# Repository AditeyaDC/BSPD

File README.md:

# BSPD RZ-XX6-C/E — Brake System Plausibility Device
**Ashwa Racing 27**  
Designed by Aditeya Sarkar

---

## What is a BSPD?

The Brake System Plausibility Device is a mandatory safety circuit in FSAE/Formula Student vehicles. Its job is to cut power to the motor (via the Shutdown Circuit / SDC) if the driver simultaneously applies heavy braking and demands significant throttle — a condition that should never happen during normal operation and indicates either a pedal fault or a stuck throttle.

This design targets the **FSG CV+EV rules** (with CV mode support via a jumper) and is built entirely out of discrete analog logic — no microcontroller involved.

---

## Block Diagram / Signal Flow

```
Connectors (BPS, TPS, SDC)
        │
        ▼
Current Sensor (EV only)          ←── Biasing circuit converts ±4V diff → 0.5–4.5V
        │
        ▼
Implausibility/Plausibility Check  ←── 500ms timer + 10s timer + comparators
        │
        ▼
SCS Check (Short Circuit Safety)
        │
        ▼
Reset System (SR latch + Power-on reset)
        │
        ▼
Relay (SDC_OUT → cuts motor power / fuel pump)
        │
        ▼
Back to Connectors
```

> Signal flow as annotated in the schematic (Sheet 1/9)

---

## Schematic Overview

The top-level sheet ties everything together. The core logic sits around a **SN74HCS14DRQ1** (Schmitt-trigger inverter, U1) and a **SN74HCS32DRQ1** (OR gate, U2), with the relay controlled by a NMOS gate driven off `RELAY_NMOS_G_BAR`.

---

## Subsystems

### 1. Power Supply

Input is +7V from the car's GLV (Grounded Low Voltage) supply. The board generates a regulated **+5V rail** using an **LDL1117S50R** LDO. Protection is handled by:

- **F1** — Polyfuse for overcurrent  
- **Q2 (STR2P3LLH6)** — P-channel MOSFET for reverse polarity protection, driven by a BC856BS transistor pair (Q1A/Q1B)
- **D1 (NZH16C)** — Zener clamp

For EV operation, isolated ±12V rails are generated via an **MPA1212S** DC-DC isolator (PS1), referenced to ISO-GND, with a Y-capacitor (C3, 10µF) for common-mode filtering.

Total board power budget: ~145–150mA (LEDs 40mA + ICs 40mA + dividers ~5mA + relay 40mA + misc).

---

### 2. Implausibility & Plausibility Check

This is the heart of the BSPD logic. Three comparator circuits run in parallel:

**Implausibility Check** (bottom-left, Sheet 9)  
- Uses **TC33X-2-103E** references and **LM339LV-Q1** comparators
- Both BPS (brake pressure) and TPS (throttle position) must exceed their respective thresholds simultaneously to flag implausibility
- Output: `Implausibility` signal (HIGH = fault)

**500ms Implausibility Timer** (top-left, Sheet 9)  
- Uses a **DMG2305UX-7** complementary MOSFET pair to charge/discharge a capacitor (C12, 10µF + C13) at a controlled rate
- When implausibility is sustained for >500ms, `500ms comparator output` goes HIGH
- The DWC2305UX-7 N-channel requirements: Vth ~1V, Ids up to 10mA → 2N7002K used
- The P-channel: Vth ~−1V, Ids ~10mA → same DWC2305UX-7 (check datasheet for exact variant)

**10s Plausibility Timer** (top-right, Sheet 9)  
- Similar RC-based timing circuit; capacitor (C13) only charges when implausibility is active
- Output: `10s comparator output` — used to latch the fault via the SR latch if the 10s window is exceeded
- `Reset_Signal_Low` can discharge the cap and reset state

---

### 3. Memory Element (SR Latch) + Power Reset

**SR Latch** (Sheet 4, left)  
Built from **SN74HC02-Q1** NOR gates (U4A/U4B):

| S (500ms) | R | Q |
|:---------:|:-:|:-:|
| 0 | 0 | Hold |
| 0 | 1 | 0 |
| 1 | 0 | 1 |

Q drives `Q_Output` and `Q_OUT_BAR`. The relay state is: `Relaybar = NOR(SCS_bar, Q)`.

So the SDC relay opens (cuts power) only when Q = 0 and SCS_bar is LOW — i.e., no fault and no short circuit detected.

**Power-on Reset** (Sheet 4, right)  
Uses an **LM339LV-Q1** comparator (U5A) with R16 (100k), R17 (47k), and C7 (10µF) to generate a ~200ms HIGH pulse on `PWR_RST` at power-on. This forces the latch into a known state (R = 1 momentarily → Q = 0). Once past the PoR window, R → 0 and normal latch operation resumes.

Two push-buttons (SW1, SW2) provide manual `Reset_Signal_High` / `Reset_Signal_Low` for bench testing.

---

### 4. SCS Short Circuit Check

The SCS (Short Circuit Safety) check uses **LM339LV-Q1** comparators (U5B/U5D/U5C) to detect wiring faults — specifically shorts to GND (<0.05V) or shorts to +5V (>4.95V) on the BPS and TPS lines.

- Normally: `SCS_Check` = HIGH (no fault)
- On short detection: goes LOW, which blocks the relay from closing regardless of Q

Thresholds set by 100k/1k voltage divider pairs on each input.

---

### 5. Current Sensor (HB0 300) Biasing (EV Only)

The current sensor (external, connected via J3) outputs a differential signal in the ±4V range. Sheet 6 handles the level shift to a 0.5V–4.5V single-ended signal suitable for the comparators.

- BAT42W Schottky diodes (D3–D6) clamp Vs+ and Vs− to the 0–5V range
- **TLV9002-Q1** op-amps (U6A/U6B) in a difference amplifier config with a +2.5V mid-rail reference
- Output: `CS_OUT` → fed into the implausibility comparator as the throttle-side signal in EV mode
- A jumper on Sheet 8 allows bypassing this for CV (combustion) mode, where TPS1_IN connects directly

---

### 6. Relay

The SDC relay is an **OJE-SH-105LMH** (U7), driven by an NMOS switch (**MMFTN3422K**, Q3) on the low side. `SDC_OUT` drives the relay coil. A **S3B5MB** diode (D7) provides flyback protection. A blue LED gives constant visual indication of relay state.

---

### 7. Connectors

All external signals come through **TE Connectivity 1744426-series** connectors:

| Connector | Signals |
|-----------|---------|
| J2 (1744426-5) | PWR_FLAG (+7V), GND, +12V, SDC_IN, SDC_OUT |
| J3 (1744426-4) | +12V(ISO), Vs−, Vs+, −12V(ISO) |
| J4 (1744426-3) | GND, BPS_IN, +12V |
| J5 (1744426-2) | TPS1_IN, GND |

BPS scaling: R42 (200Ω) + R43 (430Ω) divider sets `BPS_SCLD` in the 0.88V–4.4V window.  
ESD protection on BPS line via **ESDCAN01-2BLY** (D9).

---

### 8. Probing Points

16 dedicated test points for bench validation:

| TP | Net | TP | Net |
|----|-----|----|-----|
| TP1 | +12V | TP2 | Vref_BPS_Thresh |
| TP3 | +7V | TP4 | 500ms_Vref |
| TP5 | +5V | TP6 | 10s_Vref |
| TP7 | GND | TP8 | Vref_TPS_Thresh |
| TP9 | +12V ISO | TP10 | 10s_V |
| TP11 | GND ISO | TP12 | Q_Output |
| TP13 | −12V ISO | TP14 | 500ms_V |
| TP15 | BPS | TP16 | TPS |

---

## Key ICs

| Part | Function |
|------|----------|
| SN74HCS14DRQ1 | Schmitt-trigger inverter (signal conditioning) |
| SN74HCS32DRQ1 | OR gate (implausibility logic) |
| SN74HC02-Q1 | NOR gate SR latch (fault memory) |
| LM339LV-Q1 | Quad comparator (thresholds, SCS, power reset) |
| TLV9002-Q1 | Op-amp (current sensor biasing) |
| LDL1117S50R | 5V LDO regulator |
| MPA1212S | ±12V isolated DC-DC (EV) |
| OJE-SH-105LMH | SDC relay |
| MMFTN3422K | N-channel MOSFET (relay driver) |
| DMG2305UX-7 | Complementary MOSFET pair (timer charging) |

---

## KiCad Version Compatibility

This schematic was designed in **KiCad EDA 10.0.0**.

If you're on KiCad v9 and need to open these files, a downconverted v9-compatible version is available — reach out or raise an issue. The downconversion removes v10-specific fields (like `uuid` blocks and certain footprint attributes) that cause parse errors on older installs.

---

## Repo Structure

```
BSPD/
├── BSPD.kicad_sch              # Top-level schematic
├── Power Supply GLV.kicad_sch
├── Probing points.kicad_sch
├── Reset system.kicad_sch
├── SCS check.kicad_sch
├── Current Sensor.kicad_sch
├── Relay.kicad_sch
├── Connectors.kicad_sch
├── IMP_P_Check.kicad_sch       # Implausibility/Plausibility check
└── README.md
```

---

## Team

**Ashwa Racing — 27**  
R.V. College of Engineering, Bangalore  

Electrical & Testing Subsystem  
Schematic design: Aditeya Sarkar

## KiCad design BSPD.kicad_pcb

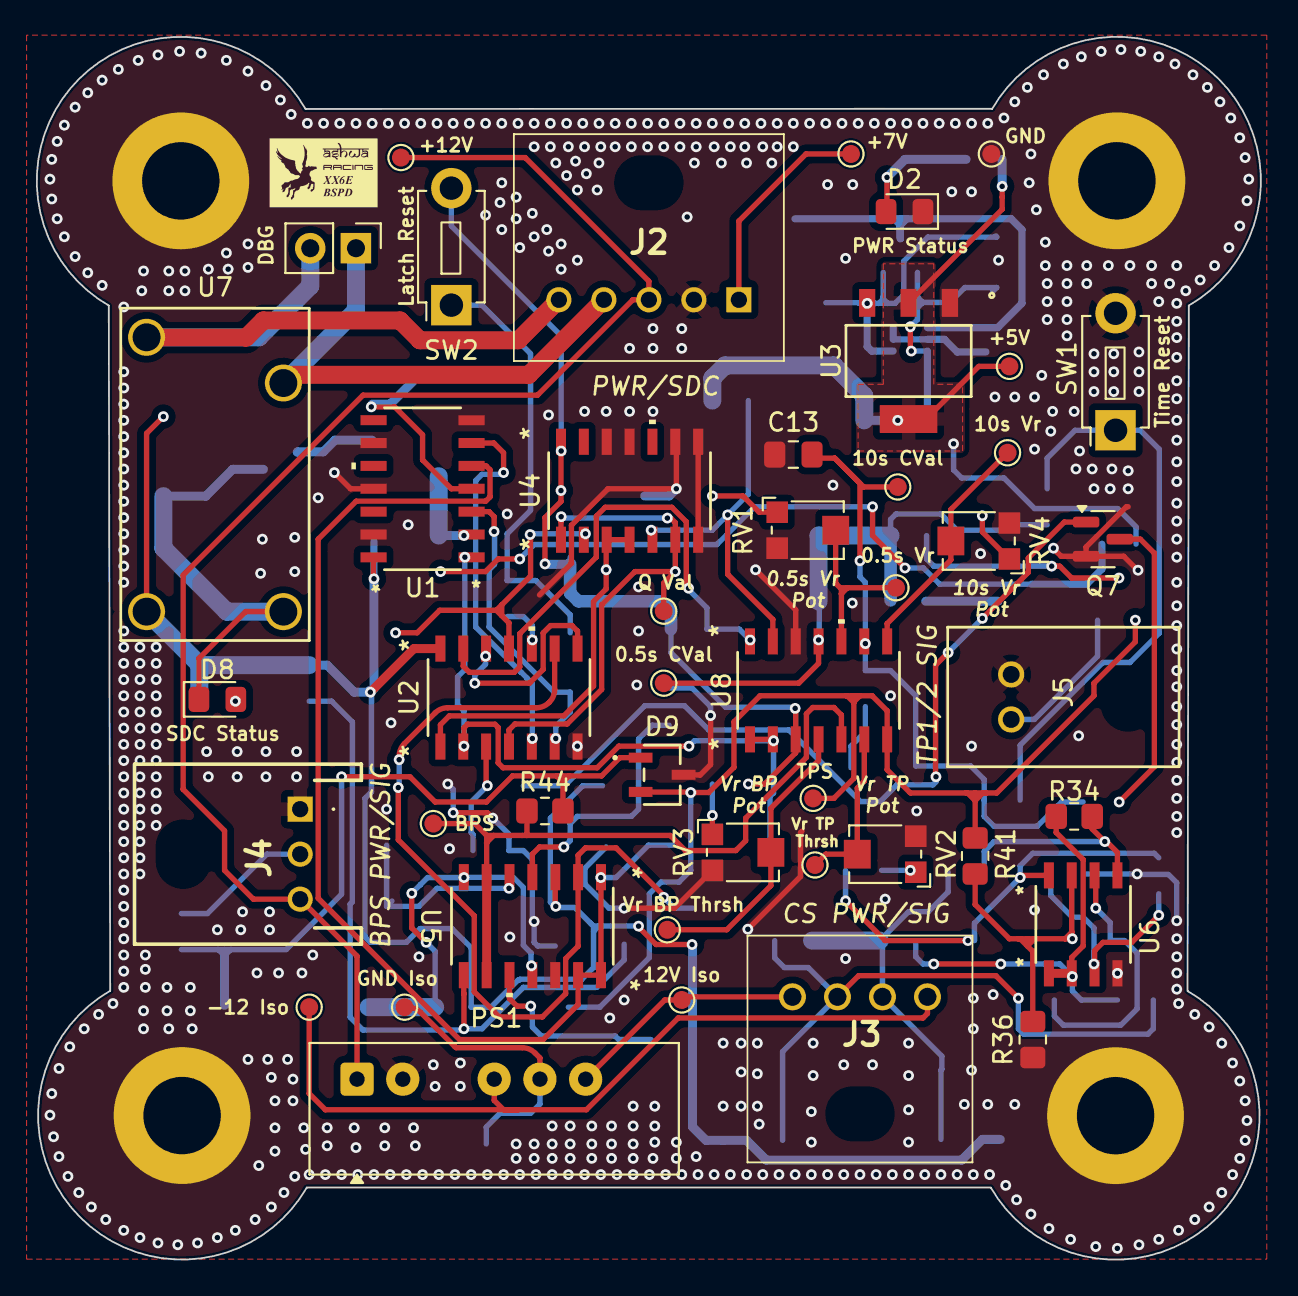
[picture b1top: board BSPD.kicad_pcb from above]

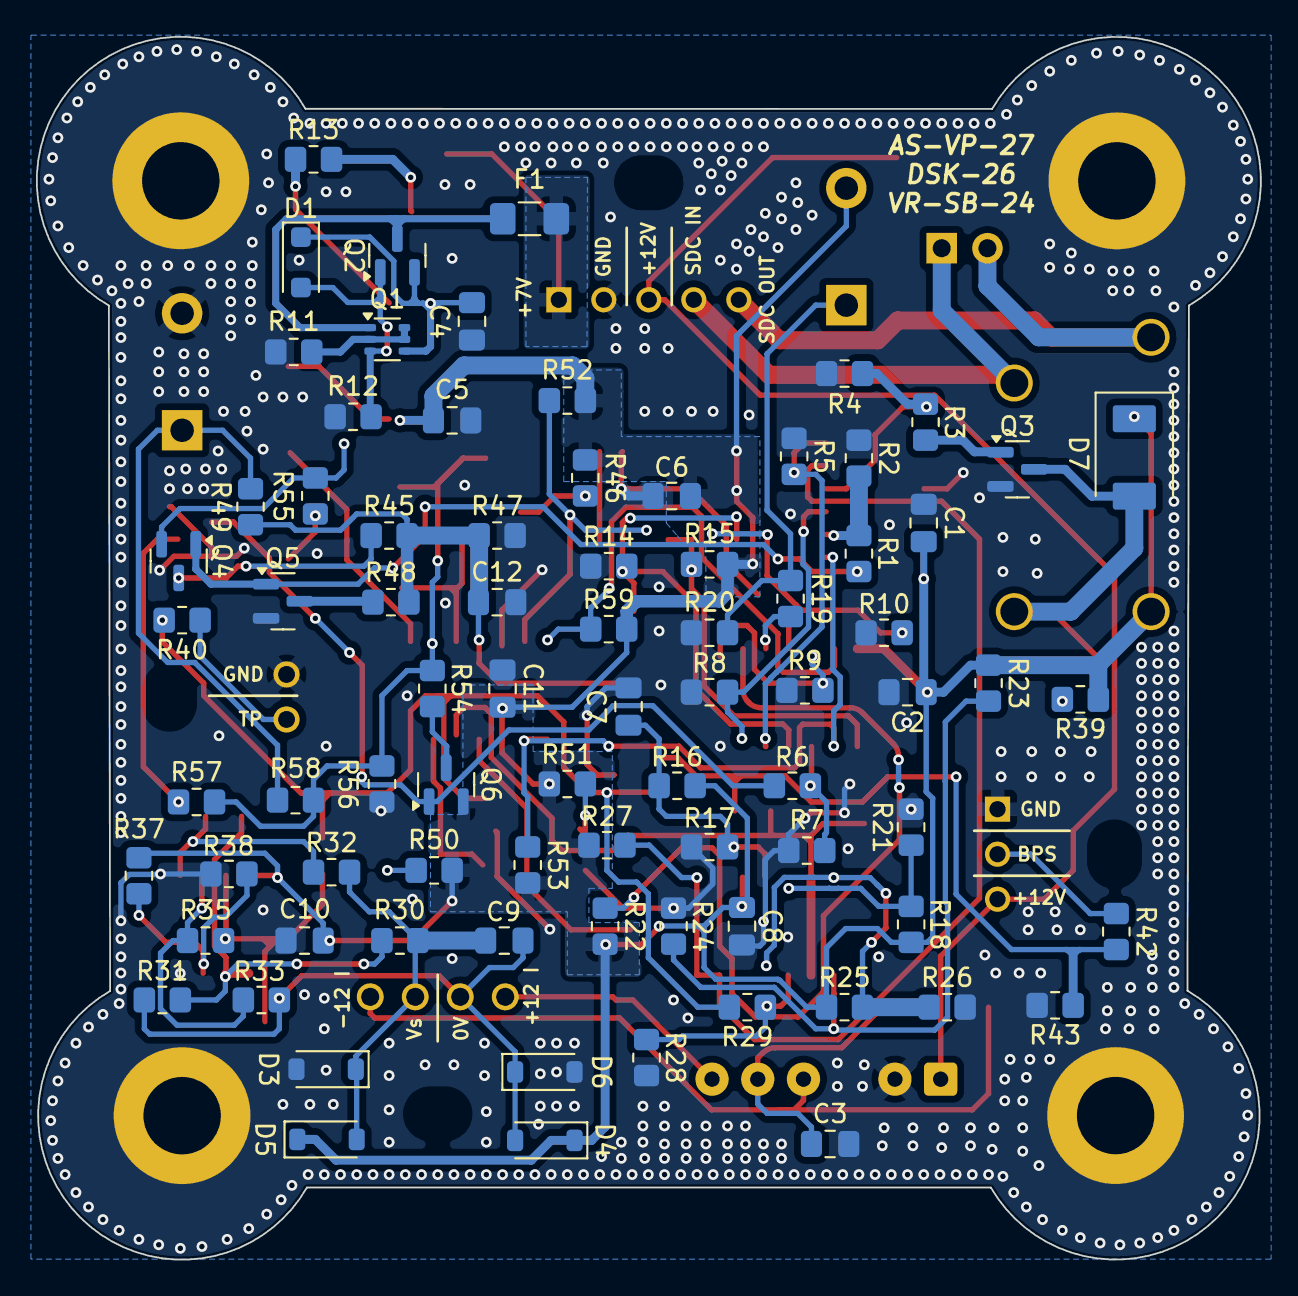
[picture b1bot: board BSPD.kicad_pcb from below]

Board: 2 copper layers, 68.0 x 67.9 mm, 129 parts (80 on the bottom side), 67 nets.

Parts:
C1, C2, C6, C8, C10, C11: 0.1u; C_0805_2012Metric_Pad1.18x1.45mm_HandSolder
C3, C7, C12, C13: 10u; C_0805_2012Metric_Pad1.18x1.45mm_HandSolder
C4, C9: 1u; C_0805_2012Metric_Pad1.18x1.45mm_HandSolder
C5: 4.7u; C_0805_2012Metric_Pad1.18x1.45mm_HandSolder
D1: NZH16C; D_SOD-123F
D2: RED LED; LED_0805_2012Metric_Pad1.15x1.40mm_HandSolder
D3, D4, D5, D6: BAT42W; D_SOD-123
D7: S3BSMB; P26_DO-214AA_SMB
D8: BLUE LED; LED_0805_2012Metric_Pad1.15x1.40mm_HandSolder
D9: ESDCAN01-2BLY; SOT_01-2BLY_STM
F1: Polyfuse; Fuse_1206_3216Metric_Pad1.42x1.75mm_HandSolder
H1, H2, H3, H4: MountingHole_Pad; MountingHole_4.3mm_M4_ISO7380_Pad
J1: Conn_01x02_Pin; PinHeader_1x02_P2.54mm_Vertical
J2: 1744426-5; 17444265
J3: 1744426-4; 17444264
J4: 1744426-3; 17444263
J5: 1744426-2; CONN2_1744426-2
PS1: MPA1212S; Converter_DCDC_XP_POWER-IAxxxxS_THT
Q1: BC856BS; SOT-363_SC-70-6
Q2: STR2P3LLH6; SOT-23
Q3: MMFTN3422K; SOT-23
Q4, Q6: DMG2305UX-7; SOT-23
Q5, Q7: 2N7002K; SOT-23
R1, R2, R3, R4, R5, R6, R7, R8, R9, R10, R14, R15, R19, R20, R21, R22, R27, R30, R31, R34, R35, R37, R38, R40, R41, R44, R46, R47, R50, R51, R52, R53, R55, R59: 10k; R_0805_2012Metric_Pad1.20x1.40mm_HandSolder
R11: 22k; R_0805_2012Metric_Pad1.20x1.40mm_HandSolder
R12: 33k; R_0805_2012Metric_Pad1.20x1.40mm_HandSolder
R13: 147; R_0805_2012Metric_Pad1.20x1.40mm_HandSolder
R16, R23, R26: 100k; R_0805_2012Metric_Pad1.20x1.40mm_HandSolder
R17: 47k; R_0805_2012Metric_Pad1.20x1.40mm_HandSolder
R18: 91k; R_0805_2012Metric_Pad1.20x1.40mm_HandSolder
R24, R25: 1k; R_0805_2012Metric_Pad1.20x1.40mm_HandSolder
R28, R29, R36: 1M; R_0805_2012Metric_Pad1.20x1.40mm_HandSolder
R32, R33: 20k; R_0805_2012Metric_Pad1.20x1.40mm_HandSolder
R39: 65; R_0805_2012Metric_Pad1.20x1.40mm_HandSolder
R42: 200; R_0805_2012Metric_Pad1.20x1.40mm_HandSolder
R43: 430; R_0805_2012Metric_Pad1.20x1.40mm_HandSolder
R45: 40k; R_0805_2012Metric_Pad1.20x1.40mm_HandSolder
R48, R49, R57, R58: 100; R_0805_2012Metric_Pad1.20x1.40mm_HandSolder
R54: 511k; R_0805_2012Metric_Pad1.20x1.40mm_HandSolder
R56: 240k; R_0805_2012Metric_Pad1.20x1.40mm_HandSolder
RV1, RV2, RV3, RV4: TC33X-2-103E; Potentiometer_Bourns_TC33X_Vertical
SW1, SW2: SW_Push; SW_PUSH_1P1T_6x3.5mm_H4.3_APEM_MJTP1243
TP1: 12V; TestPoint_Pad_D1.0mm
TP2: Vref BPS Thresh; TestPoint_Pad_D1.0mm
TP3: 7V; TestPoint_Pad_D1.0mm
TP4: 0.5 Vref; TestPoint_Pad_D1.0mm
TP5: 5V; TestPoint_Pad_D1.0mm
TP6: 10 Vref; TestPoint_Pad_D1.0mm
TP7: GND; TestPoint_Pad_D1.0mm
TP8: Vref TPS Thresh; TestPoint_Pad_D1.0mm
TP9: 12V ISO; TestPoint_Pad_D1.0mm
TP10: 10s V; TestPoint_Pad_D1.0mm
TP11: GND ISO; TestPoint_Pad_D1.0mm
TP12: Q; TestPoint_Pad_D1.0mm
TP13: -12V ISO; TestPoint_Pad_D1.0mm
TP14: 0.5 V; TestPoint_Pad_D1.0mm
TP15: BPS; TestPoint_Pad_D1.0mm
TP16: TPS; TestPoint_Pad_D1.0mm
U1: SN74HCS14DRQ1; SOIC_S14DR_TEX
U2: SN74HCS32DRQ1; SOIC_S14DR_TEX
U3: LDL1117S50R; SOT223_STM
U4: SN74HC02-Q1; SOIC_S14DR_TEX
U5, U8: LM339LV-Q1; SOIC_S14DR_TEX
U6: TLV9002-Q1; SOIC8_D_TEX
U7: OJE-SH-105LMH_000; RELAY4_OJE-SH-105LMH_000_TEC

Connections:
10s comparator output: R59.1, U2.13 (4B), U8.14
10s_CAP_PMOS: Q6.1 (G), Q7.1 (G), R6.1
10s_V: C13.1, R54.2, R56.1, R57.1, R58.1, TP10.1, U8.9 (+)
10s_Vref: RV4.2, TP6.1, U8.8 (-)
500ms comparator output: R52.2, U4.5, U8.13
500ms_V: C12.1, R45.2, R47.1, R48.2, R49.1, TP14.1, U8.11 (+)
500ms_Vref: RV1.2, TP4.1, U8.10 (-)
+0.05V: R23.2, R24.1, U5.8 (-)
+2.5V: R30.2, R31.1, R34.2, U6.1, U6.2 (-)
+4.95V: R25.2, R26.1, U5.7 (+), U5.11 (+)
+5V: C1.1, C2.1, C5.1, C6.1, C8.1, C10.1, C11.1, D4.1 (K), D5.1 (K), D7.1 (K), Q4.2 (S), Q6.2 (S), R13.1, R15.1, R16.1, R18.1, R22.2, R23.1, R25.1, R27.2, R37.1, R39.1, R46.1, R50.1, R51.1, R52.1, R53.2, R55.1, R59.2, SW2.2, TP5.1, U1.14 (VCC), U2.14 (VCC), U3.2 (VOUT), U3.4 (VOUT), U4.14 (VCC), U5.3 (V+), U6.8 (V+), U7.2, U8.3 (V+)
+7V: F1.1, J2.1, TP3.1
+12V: J2.3, J4.3, PS1.1 (+Vin), TP1.1
+12V(ISO): J3.1, PS1.6 (+Vout), TP9.1
-12V(ISO): J3.4, PS1.4 (-Vout), TP13.1
BPS: R44.2, TP15.1, U5.6 (-), U5.9 (+), U8.5 (+)
BPS_IN: J4.2, R42.1
BPS_SCLD: D9.1 (K), R42.2, R43.1, R44.1
CS_OUT: R35.1, R36.2, R41.2, U6.7
GND: C1.2, C2.2, C3.2, C4.2, C5.2, C6.2, C7.2, C8.2, C10.2, C11.2, C12.2, C13.2, D2.1 (K), D3.2 (A), D6.2 (A), D9.3 (A), H1.1, H2.1, H3.1, H4.1, J2.2, J4.1, J5.2, PS1.2 (-Vin), Q3.2 (S), Q5.2 (S), Q7.2 (S), R2.1, R4.1, R5.1, R7.1, R8.1, R9.1, R10.1, R11.2, R12.2, R14.1, R17.2, R20.2, R21.2, R24.2, R26.2, R28.1, R36.1, R38.2, R43.2, R47.2, R56.2, RV1.3, RV2.3, RV3.3, RV4.3, SW1.2, TP7.1, U1.7 (GND), U1.9 (4A), U1.11 (5A), U1.13 (6A), U2.7 (GND), U3.1 (GND), U4.7 (GND), U4.8, U4.9, U4.11, U4.12, U5.12 (V-), U6.4 (V-), U8.12 (V-)
IMP_BAR: Q4.1 (G), Q5.1 (G), R1.1
ISO-GND: C3.1, PS1.5 (0V), TP11.1
Implausiblity: R53.1, U1.1 (1A), U2.2 (1B), U8.1, U8.2
unnamed: D1.2 (A), Q1.3 (C2), Q2.1 (G), R12.1
unnamed: C4.1, D1.1 (K), Q1.4 (E2), Q2.2 (S), U3.3 (VIN)
unnamed: D2.2 (A), R13.2
unnamed: D7.2 (A), D8.1 (K), Q3.3 (D), U7.1
unnamed: D8.2 (A), R39.2
unnamed: Q1.2 (B1), Q1.5 (B2), Q1.6 (C1), R11.1
unnamed: F1.2, Q1.1 (E1), Q2.3 (D)
unnamed: Q4.3 (D), R45.1
unnamed: Q5.3 (D), R48.1
unnamed: Q6.3 (D), R54.1
unnamed: Q7.3 (D), R57.2
unnamed: R19.2, R20.1, SW2.1
unnamed: R46.2, RV1.1
unnamed: R50.2, RV2.1
unnamed: R51.2, RV3.1
unnamed: R55.2, RV4.1
unnamed: R1.2, R2.2, U1.2 (1Y)
unnamed: R3.2, R4.2, U1.4 (2Y)
unnamed: R6.2, R7.2, U2.3 (1Y)
unnamed: R9.2, U2.8 (3Y), U2.12 (4A)
unnamed: R18.2, R21.1, U5.5 (+)
unnamed: C7.1, R16.2, R17.1, U5.4 (-)
unnamed: R28.2, R29.1, U5.10 (-)
unnamed: R37.2, R38.1, U6.3 (+)
unnamed: R32.2, R34.1, U6.5 (+)
unnamed: R33.1, R35.2, U6.6 (-)
PWR_RST: R22.1, U2.9 (3A), U5.2
Q_OUT_BAR: R15.2, U2.1 (1A), U4.3, U4.4
Q_Output: R14.2, TP12.1, U2.4 (2A), U4.1, U4.6
R input: R10.2, U2.11 (4Y), U4.2
RELAY_NMOS_G: R8.2, U1.3 (2A), U2.6 (2Y)
RELAY_NMOS_G_BAR: Q3.1 (G), R3.1
Reset_Signal_High: R19.1, U2.10 (3B)
Reset_Signal_Low: R49.2, R58.2, SW1.1
SCS_Check: R27.1, U1.5 (3A), U5.1, U5.13, U5.14
SCS_Check_BAR: R5.2, U1.6 (3Y), U2.5 (2B)
SDC_IN: J1.1, J2.4, U7.3
SDC_OUT: J1.2, J2.5, U7.4
TPS: D9.2 (K), R29.2, R40.2, R41.1, TP16.1, U8.7 (+)
TPS1_IN: J5.1, R40.1
Vref_BPS_Thresh: RV3.2, TP2.1, U8.4 (-)
Vref_TPS_Thresh: RV2.2, TP8.1, U8.6 (-)
Vs+: C9.1, D3.1 (K), D5.2 (A), J3.3, R30.1, R32.1
Vs-: C9.2, D4.2 (A), D6.1 (K), J3.2, R31.2, R33.2

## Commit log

2026-03-28 Final board design commit
